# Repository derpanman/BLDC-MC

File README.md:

# BLDC-MC
CAD, diagrams, and code related to a BLDC motor controller project for Cal SMV

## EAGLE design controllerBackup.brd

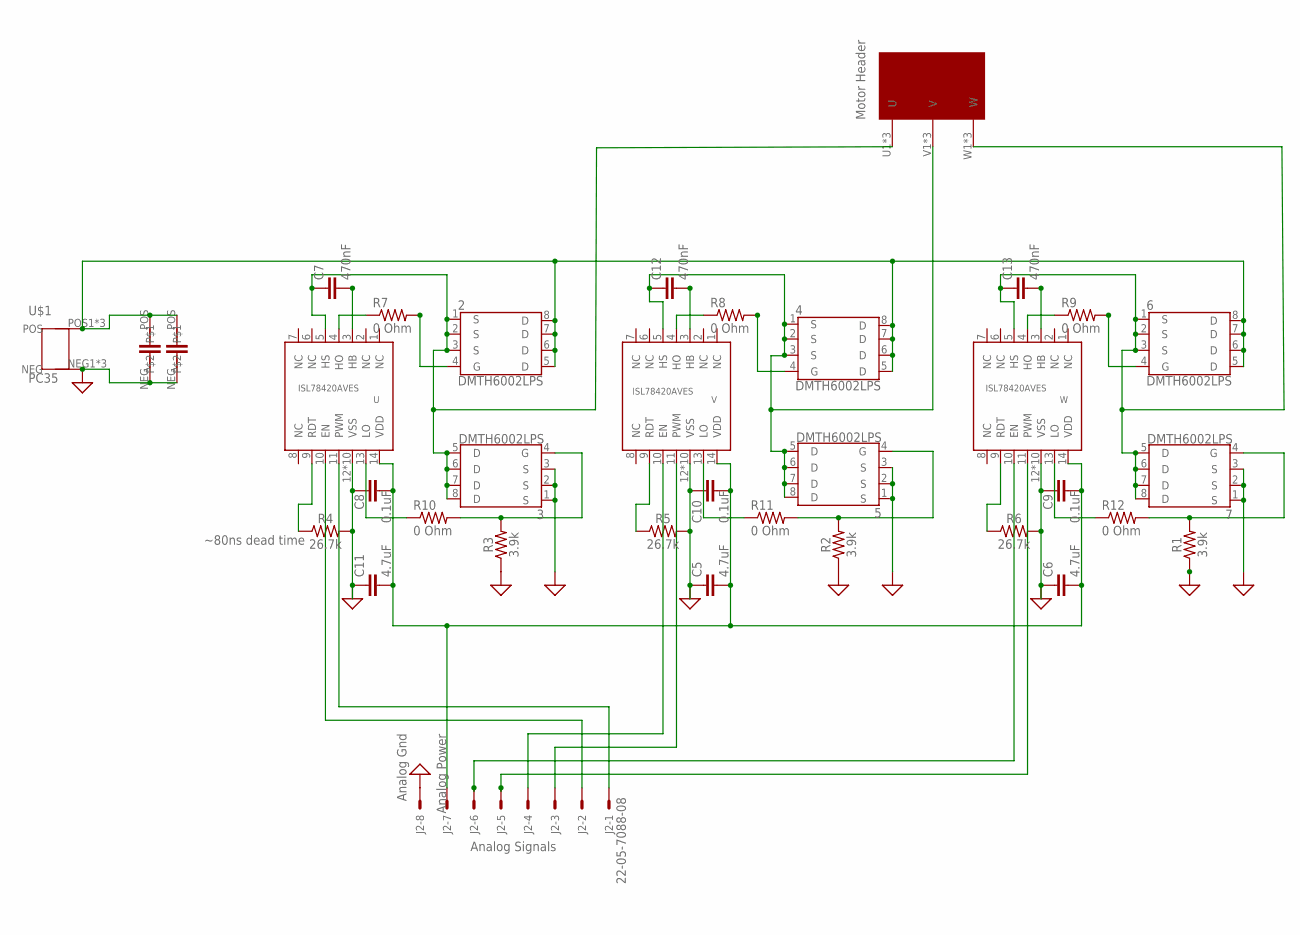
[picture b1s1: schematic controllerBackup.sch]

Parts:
2, 3, 4, 5, 6, 7: DMTH6002LPS; POWERDI5060
C5, C6, C11: 4.7uF; 0603
C7, C12, C13: 470nF; 0402
C8, C9, C10: 0.1uF; 0603
J2: 22-05-7088-08; 7395-08
R1, R2, R3: 3.9k; 0603
R4, R5, R6: 26.7k; 0603
R7, R8, R9, R10, R11, R12: 0 Ohm; R0603
U: ISL78420AVES; 14LDHTSSOP
U$1: PC35; PC35.1762741
U$2: PC35_3; PC35.1762754
U$3, U$4: 1mF 63V; MAL2146998
V: ISL78420AVES; 14LDHTSSOP
W: ISL78420AVES; 14LDHTSSOP

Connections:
0: 2.1 (S), 2.2 (S), 2.3 (S), 3.5 (D), 3.6 (D), 3.7 (D), 3.8 (D), C7.1, U.5 (HS), U$2.U1 (U), U$2.U2 (U), U$2.U3 (U)
GND: 3.1 (S), 3.2 (S), 3.3 (S), 5.1 (S), 5.2 (S), 5.3 (S), 7.1 (S), 7.2 (S), 7.3 (S), C5.1, C6.1, C8.1, C9.1, C10.1, C11.1, J2.8, R1.1, R2.1, R3.1, R4.2, R5.2, R6.2, U.12 (VSS), U.EPAD (VSS), U.P$1 (VSS), U.P$2 (VSS), U.P$3 (VSS), U.P$4 (VSS), U.P$5 (VSS), U.P$6 (VSS), U.P$7 (VSS), U.P$8 (VSS), U$1.NEG1 (NEG), U$1.NEG2 (NEG), U$1.NEG3 (NEG), U$3.NEG, U$4.NEG, V.12 (VSS), V.EPAD (VSS), V.P$1 (VSS), V.P$2 (VSS), V.P$3 (VSS), V.P$4 (VSS), V.P$5 (VSS), V.P$6 (VSS), V.P$7 (VSS), V.P$8 (VSS), W.12 (VSS), W.EPAD (VSS), W.P$1 (VSS), W.P$2 (VSS), W.P$3 (VSS), W.P$4 (VSS), W.P$5 (VSS), W.P$6 (VSS), W.P$7 (VSS), W.P$8 (VSS)
unnamed: J2.1, U.11 (PWM)
unnamed: R10.1, U.13 (LO)
unnamed: C5.2, C6.2, C8.2, C9.2, C10.2, C11.2, J2.7, U.14 (VDD), V.14 (VDD), W.14 (VDD)
unnamed: C7.2, U.3 (HB)
unnamed: J2.2, U.10 (EN)
unnamed: 4.4 (G), R8.2
unnamed: 2.4 (G), R7.2
unnamed: 3.4 (G), R3.2, R10.2
unnamed: J2.3, V.11 (PWM)
unnamed: J2.4, V.10 (EN)
unnamed: 5.4 (G), R2.2, R11.2
unnamed: 6.4 (G), R9.2
unnamed: 7.4 (G), R1.2, R12.2
unnamed: 4.1 (S), 4.2 (S), 4.3 (S), 5.5 (D), 5.6 (D), 5.7 (D), 5.8 (D), C12.1, U$2.V1 (V), U$2.V2 (V), U$2.V3 (V), V.5 (HS)
unnamed: C12.2, V.3 (HB)
unnamed: C13.2, W.3 (HB)
unnamed: 6.1 (S), 6.2 (S), 6.3 (S), 7.5 (D), 7.6 (D), 7.7 (D), 7.8 (D), C13.1, U$2.W1 (W), U$2.W2 (W), U$2.W3 (W), W.5 (HS)
unnamed: R4.1, U.9 (RDT)
unnamed: R5.1, V.9 (RDT)
unnamed: R6.1, W.9 (RDT)
unnamed: R8.1, V.4 (HO)
unnamed: R9.1, W.4 (HO)
unnamed: J2.5, W.11 (PWM)
unnamed: J2.6, W.10 (EN)
unnamed: R11.1, V.13 (LO)
unnamed: R12.1, W.13 (LO)
unnamed: R7.1, U.4 (HO)
unnamed: 2.5 (D), 2.6 (D), 2.7 (D), 2.8 (D), 4.5 (D), 4.6 (D), 4.7 (D), 4.8 (D), 6.5 (D), 6.6 (D), 6.7 (D), 6.8 (D), U$1.POS1 (POS), U$1.POS2 (POS), U$1.POS3 (POS), U$3.POS, U$4.POS

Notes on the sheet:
Analog Power
Analog Signals
~80ns dead time
Analog Gnd

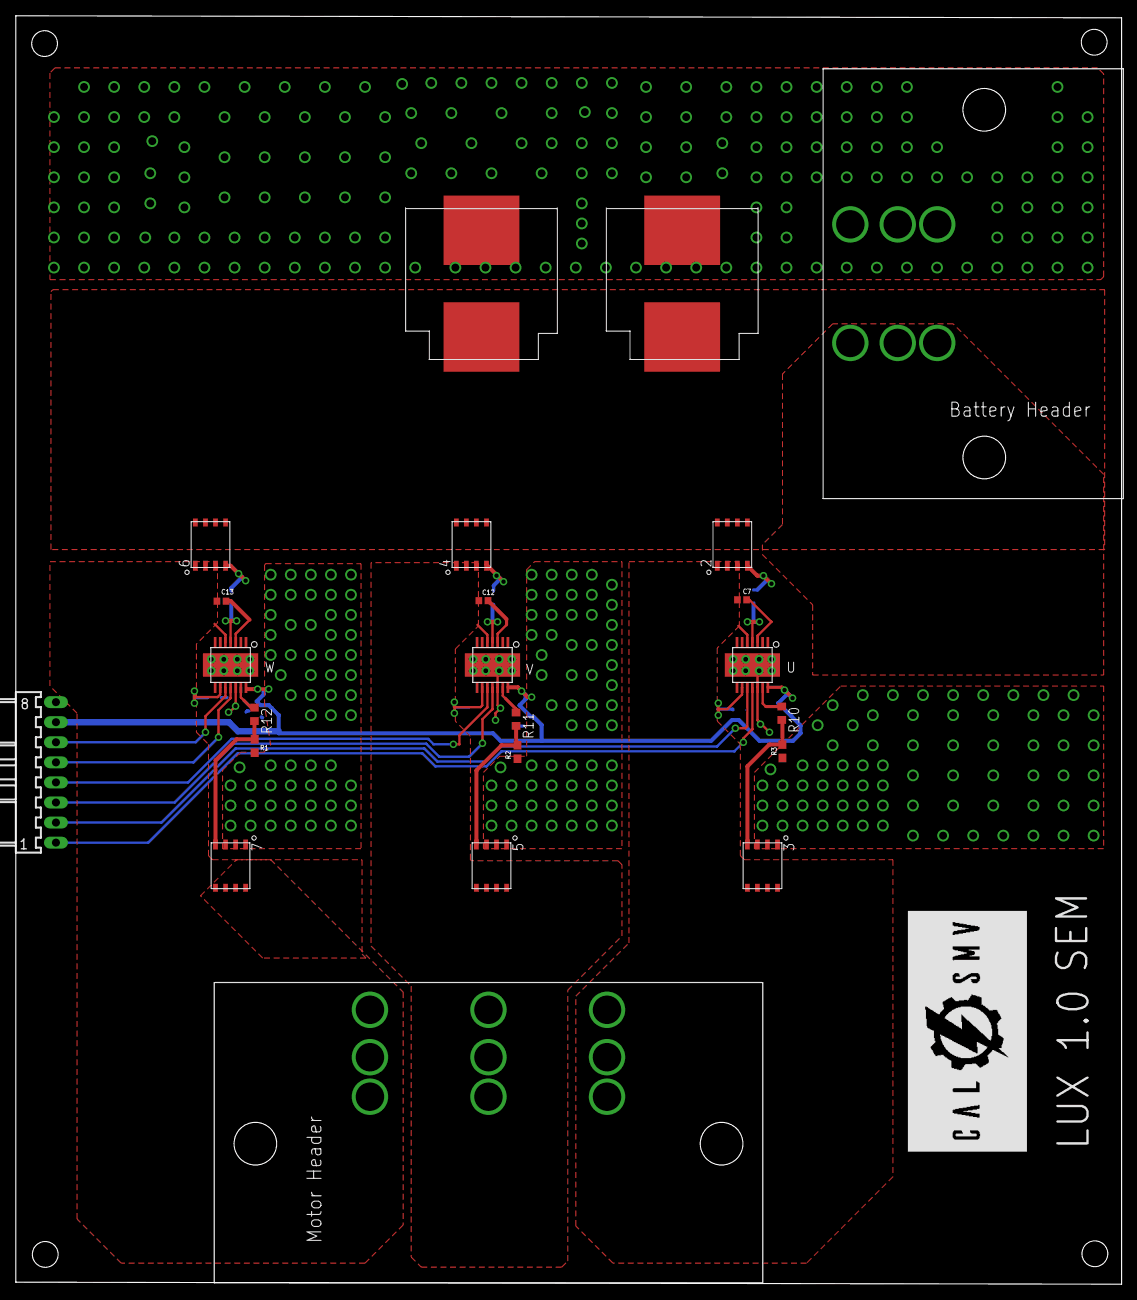
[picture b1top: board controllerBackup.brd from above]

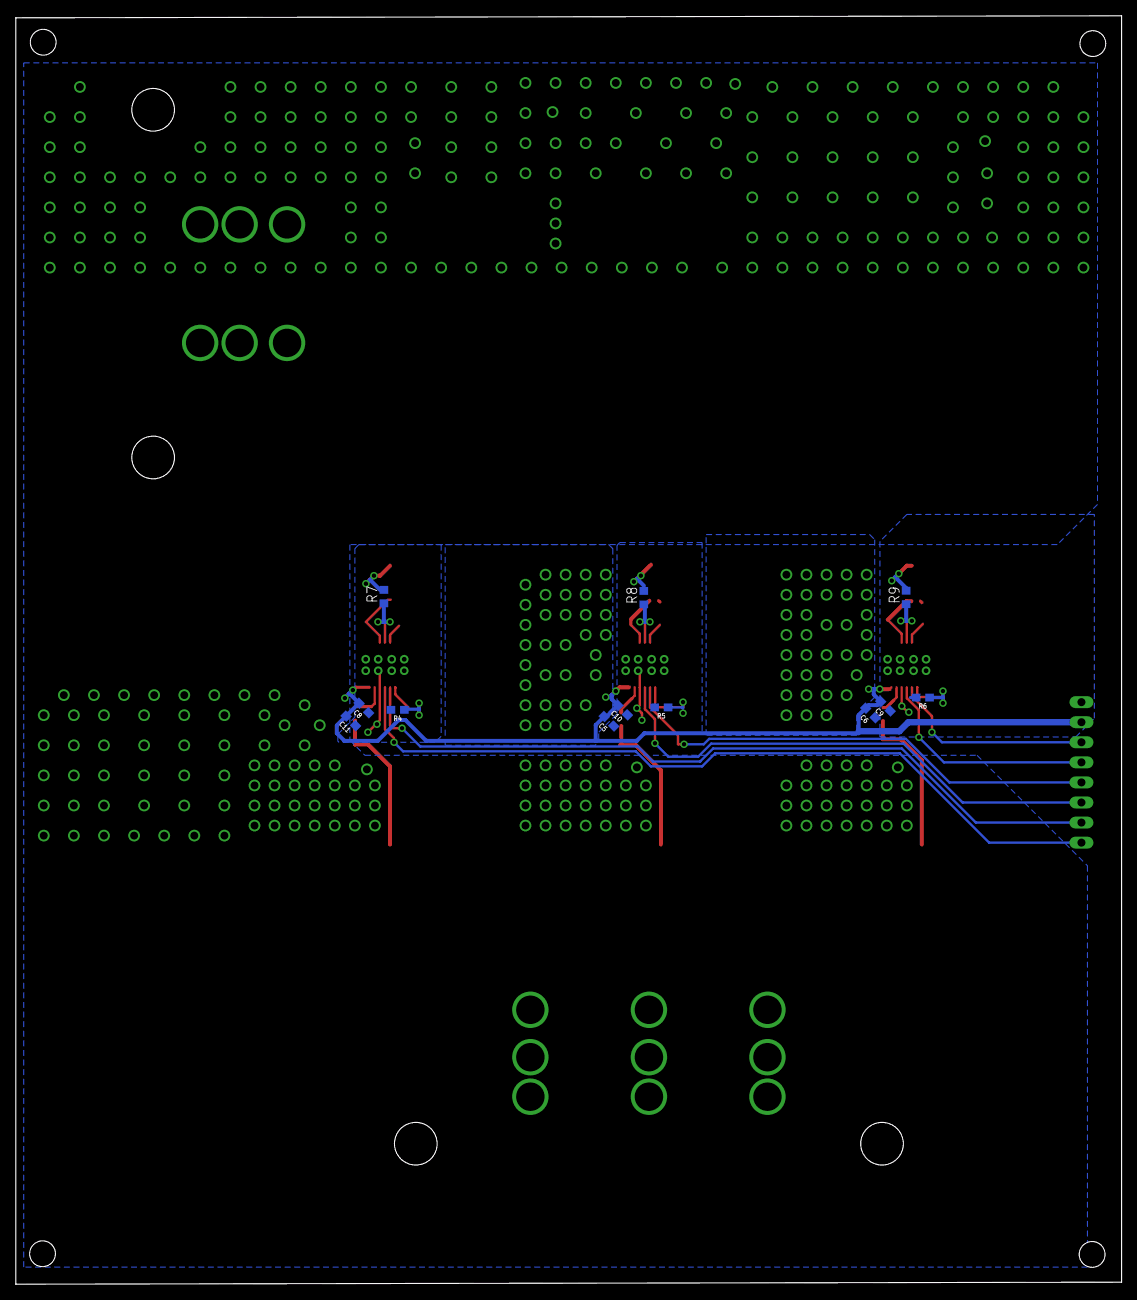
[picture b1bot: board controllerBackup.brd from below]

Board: 2 copper layers, 139.9 x 160.5 mm, 35 parts (12 on the bottom side), 30 nets.

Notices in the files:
parts and their libraries:
SparkFun-Capacitors: Licensing: Creative Commons ShareAlike 4.0 International - https://creativecommons.org/licenses/by-sa/4.0
